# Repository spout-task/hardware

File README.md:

# SPOUT hardware

Hardware for a **SPOUT** rig, part of the [spout-task](https://github.com/spout-task) project.
Every device has its own folder with design files, pictures and a README that explains what it does,
what to buy, how to make it and how to connect it to SPOUT.

A complete rig costs about **1,080 USD** (about 1,440 USD including a computer and screen).
The full bill of materials is in [`SPOUT_BOM.xlsx`](SPOUT_BOM.xlsx) and [`SPOUT_BOM.pdf`](SPOUT_BOM.pdf).

<p align="center"><em>A SPOUT rig seen from above: head restrained setup (left), motorized manipulator with the spouts (center), electronics with the Teensy breakout board (top), water reservoirs (top right) and the stepper motor driver box (right).</em></p>

## Devices

| Group | Device | What it does | How it is made | Folder |
|---|---|---|---|---|
| Electronics | Teensy breakout board | Carries the Teensy 4.1, drives the solenoids and brings out all inputs and outputs | PCB, 3D printed housing | [`teensy_breakout_board`](teensy_breakout_board/) |
| Electronics | Dual lick detector | Detects licks on one or two spouts with sub millisecond precision | PCB, 3D printed housing | [`dual_lick_detector`](dual_lick_detector/) |
| Electronics | Optogenetics power modulator | Turns a Teensy PWM signal into a 0 to 5 V analog command, so light power can be set per trial | Hand built circuit, 3D printed housing | [`optogenetics_power_modulator`](optogenetics_power_modulator/) |
| Head fixation | Head restrained setup | Headplates and holders for behavior and for two photon imaging | Laser cut titanium headplates, machined aluminium holders, ramps and cone | [`head-restrained_setup`](head-restrained_setup/) |
| Head fixation | Breadboards | Rig base plate and round base for the head fixation | Machined aluminium by a machine shop (or bought) | [`breadboards`](breadboards/) |
| Spout positioning | Motorized manipulator | Three axis stepper stage that positions the spouts | Bought stages and drivers, 3D printed adapters, laser cut driver box and drilling templates | [`motorized_manipulator`](motorized_manipulator/) |
| Spout positioning | Spout holder | Holds the stainless steel lick spout(s) and the two solenoid valves | 3D printed spout holders, laser cut solenoid holder | [`spout_holder`](spout_holder/) |
| Miscellaneous | Housings | Boxes for the audio amplifier and for the power distribution breadboard | 3D printed | [`housing_miscellaneous`](housing_miscellaneous/) |

## Build order for one rig

1. **Base.** The 12 x 18 inch breadboard is the base of the rig.
2. **Head fixation.** Build the head restrained setup on the round breadboard: magnetic base, post, clamp, aluminium tube and headplate holders.
3. **Water delivery.** Reservoir syringes, 3 way valves, solenoids in the solenoid holder, Tygon tubing, and the spouts in the spout holder.
4. **Spout positioning.** Stack the three linear stages with the printed adapters, mount the spout holder on a post on the top stage, and put the three drivers in the laser cut box.
5. **Electronics.** Teensy breakout board in its housing, power distribution box, dual lick detector in its housing. Connect the spouts to the lick detector and ground the mouse through the aluminium tube.
6. **Sound.** Audio amplifier in its housing and two speakers on short posts.
7. **Optogenetics (optional).** Optogenetics power modulator between the Teensy and the LED or AOM driver.
8. **Software.** Flash the firmware and open the GUI, see the [software](https://github.com/spout-task/software) repository.

Photos of the build process will be added.

## Conventions

* 3D printed parts: Prusa MK3, PLA, standard settings.
* Screws: 1/4 20 for the breadboards and posts, 4-40 for small parts.
* Units: mm, except the breadboard STEP files (inch). DXF files are in mm.
* Each device folder has a `design` folder with `files` (design files) and `pictures` (renders). Electronics also have a `PCB` or `circuit` folder, and the manipulator a `schematics` folder.
* File types: STL to 3D print, DXF to laser cut, STEP to edit in CAD or to send to a machine shop. Flat parts come as DXF and STL, so you can laser cut or print them.
* Each README lists for every part how we made it and from what material.

## Related repositories
[software](https://github.com/spout-task/software), [analyses](https://github.com/spout-task/analyses), [settings](https://github.com/spout-task/settings), [example_data](https://github.com/spout-task/example_data)

## License
All hardware designs in this repository are released under **CERN-OHL-S-2.0** ([`LICENSE`](LICENSE)).
The dual lick detector and the Teensy breakout board were designed by the
[HMS Research Instrumentation Core](https://github.com/HMS-RIC), whose members are authors of SPOUT,
and are shared here as part of SPOUT. Newer revisions are developed in the HMS RIC repositories for the
[lick detector](https://github.com/HMS-RIC/2-Channel-Lick-Detector) and the
[Teensy breakout board](https://github.com/HMS-RIC/Teensy-Breakout-general-purpose).

## How to cite
See [`CITATION.cff`](CITATION.cff) and the [project overview](https://github.com/spout-task).

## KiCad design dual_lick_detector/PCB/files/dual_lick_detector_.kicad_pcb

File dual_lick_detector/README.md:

# Dual lick detector

Two channel lick detector for head restrained mice. Each lick closes a tiny current path between the
spout and the grounded mouse; the detector turns that into a clean digital pulse for the Teensy, with
sub millisecond precision.

## At a glance

| | |
|---|---|
| Function | Detects licks on one or two spouts |
| Design | HMS Research Instrumentation Core, revision Alpha1e (KiCad 10) |
| Fabrication | PCB with commercial assembly, 3D printed housing |
| Approximate cost | 100 USD for the assembled board |
| Used by | SPOUT1 (one channel) and SPOUT2 (two channels) |

## Key features

* Battery powered, optically isolated front end.
* Adjustable threshold and (optionally) adjustable hysteresis (100 mV default).
* Multi turn potentiometers for fine adjustment; can be fitted with a scale dial.
* Selectable conduction mode or junction potential mode. SPOUT uses conduction mode.
* Power from micro USB or a barrel jack adapter.
* Indicator LEDs for power and lick detection; ESD protected front end.
* Optional input protection diodes to support shock delivery.

## How it works in SPOUT

In conduction mode each spout is pulled up to 9 V (from a 9 V battery) through a 4.7 MOhm resistor.
When the grounded mouse touches the spout, the voltage drops and a comparator switches. The input is
filtered with a 10 us RC filter and the comparator has 100 mV hysteresis. An optically isolated output
stage, powered by a separate 3 V adapter, drives the output through a 50 Ohm source termination, so the
signal can run over BNC cables. In the SPOUT configuration the output is active low.

## Files

| File | What it is |
|---|---|
| [`PCB/files/dual_lick_detector_.kicad_sch`](PCB/files/dual_lick_detector_.kicad_sch) | Schematic (KiCad 10) |
| [`PCB/files/dual_lick_detector_.kicad_pcb`](PCB/files/dual_lick_detector_.kicad_pcb) | Board layout (KiCad 10) |
| [`ComparatorLickDet_BOM.pdf`](ComparatorLickDet_BOM.pdf) | Component list, readable version (made for revision Alpha1d) |
| [`PCB/pictures`](PCB/pictures/) | Photos and board renders, see below |

| Part | Files | What it is | How we made it |
|---|---|---|---|
| Housing | [`.stl`](design/files/box_dual_lick_detector.stl), [`.step`](design/files/box_dual_lick_detector.step) | Housing, 152 x 89 x 20 mm, with mounting ears | 3D printed, PLA |

The SPOUT paper used revision Alpha1d (EAGLE). Alpha1e is the KiCad version of that design.
Newer revisions are developed in the [HMS RIC repository](https://github.com/HMS-RIC/2-Channel-Lick-Detector).

### Pictures

| Picture | What it shows |
|---|---|
| [`dual_lick_detector_1.jpg`](PCB/pictures/dual_lick_detector_1.jpg) | Assembled board with BNC connectors, potentiometers and battery holder |
| [`dual_lick_detector_2.jpg`](PCB/pictures/dual_lick_detector_2.jpg) | Bare board, top |
| [`dual_lick_detector_3.jpg`](PCB/pictures/dual_lick_detector_3.jpg) | Bare board, bottom |
| [`dual_lick_detector_schematic_1.png`](PCB/pictures/dual_lick_detector_schematic_1.png) | Board render from KiCad, bottom |
| [`dual_lick_detector_schematic_2.png`](PCB/pictures/dual_lick_detector_schematic_2.png) | Board render from KiCad, top |

## Bill of materials

| Qty | Part | Supplier | Part number | Price (USD) |
|---|---|---|---|---|
| 1 | Assembled lick detector board | Any PCB assembler (we used PCBWay) | KiCad files | 100 |
| 1 | 3D printed housing | | | |
| 1 | 9 V battery | | | |
| 1 | Power adapter 3 V (output stage) | NC | BY0301&BK | 5.57 |
| 1 | Stainless steel tube for the spouts | McMaster-Carr | 5560K72 | 3.90 |
| 1 | Banana socket and plug (mouse ground) | | | 2.98 |

Full list: [`SPOUT_BOM.xlsx`](../SPOUT_BOM.xlsx).

## Ordering the PCB

The board is designed in KiCad 10. Open the `.kicad_pcb` file in KiCad (free, [kicad.org](https://www.kicad.org)) and export
what your fabricator needs: Gerber and drill files (File, Fabrication Outputs), and for commercial assembly the
component list and the position file from the same menu. Default manufacturing settings are fine.

## Fabrication

1. Order the assembled board as described above. All the fine soldering will be done, you only need to solder big components on the PCB. The SPOUT boards were made and assembled by PCBWay.
2. On both sides of the PCB, solder dual jack BNC connectors in place.
3. On the top side of the PCB, you will have to solder two multi-turn potentiometers in place.
4. On the bottom side of the PCB, a DC barrel jack power connector (3V to send TTL to Teensy) and/or micro USB connector (5V if you want to send a TTL to an Arduino), a two-way toggle switch, and a 9V battery casing should be soldered in place.
5. Print `box_dual_lick_detector.stl` on a Prusa MK3 in PLA with standard settings. Mount the board with 4-40 screws and the housing on the breadboard with 1/4 20 screws.

## Assembly

1. Mount the board in the housing and the housing on the breadboard.
2. Connect the spouts to the inputs, and the outputs to the Teensy breakout board, as listed below.
3. Ground the mouse: connect the detector ground to the aluminium tube of the head restrained setup with the banana plug and socket.
4. Insert the 9 V battery and connect the 3 V adapter.
5. For imaging, split the lick outputs with a BNC T connector to your DAQ as well.

## Connections

Seen from the top, with the potentiometers facing up. Each side has two BNC connectors, one above the other.

| Part | SPOUT2 (two spouts) | SPOUT1 (one spout) |
|---|---|---|
| Left BNC, top | Left lick output, to PIN14_A0 on the Teensy breakout board | Lick output, to PIN14_A0 |
| Left BNC, bottom | Right lick output, to PIN41_A17 | Not used |
| Right BNC, top | Left lick input, from the left spout | Lick input, from the spout |
| Right BNC, bottom | Right lick input, from the right spout | Not used |
| Bottom LED | Left lick detected | Lick detected |
| Top LED | Right lick detected | Not used |
| Left potentiometer | Left lick threshold | Lick threshold |
| Right potentiometer | Right lick threshold | Not used |

## Testing and calibration

1. Touch a spout with one hand while touching the ground (aluminium tube) with the other: the lick LED lights up and the GUI shows the lick.
2. Set the threshold with the multi turn potentiometer (left for the left spout, right for the right spout) so a touch is detected reliably while the idle spout stays silent. Set it per rig, because cable length and grounding differ.

## License and attribution
Designed and developed by the [HMS Research Instrumentation Core](https://github.com/HMS-RIC), whose
members are authors of SPOUT, and shared here as part of SPOUT under **CERN-OHL-S-2.0**
([`LICENSE`](../LICENSE)). Newer revisions are developed in the
[HMS RIC repository](https://github.com/HMS-RIC/2-Channel-Lick-Detector).

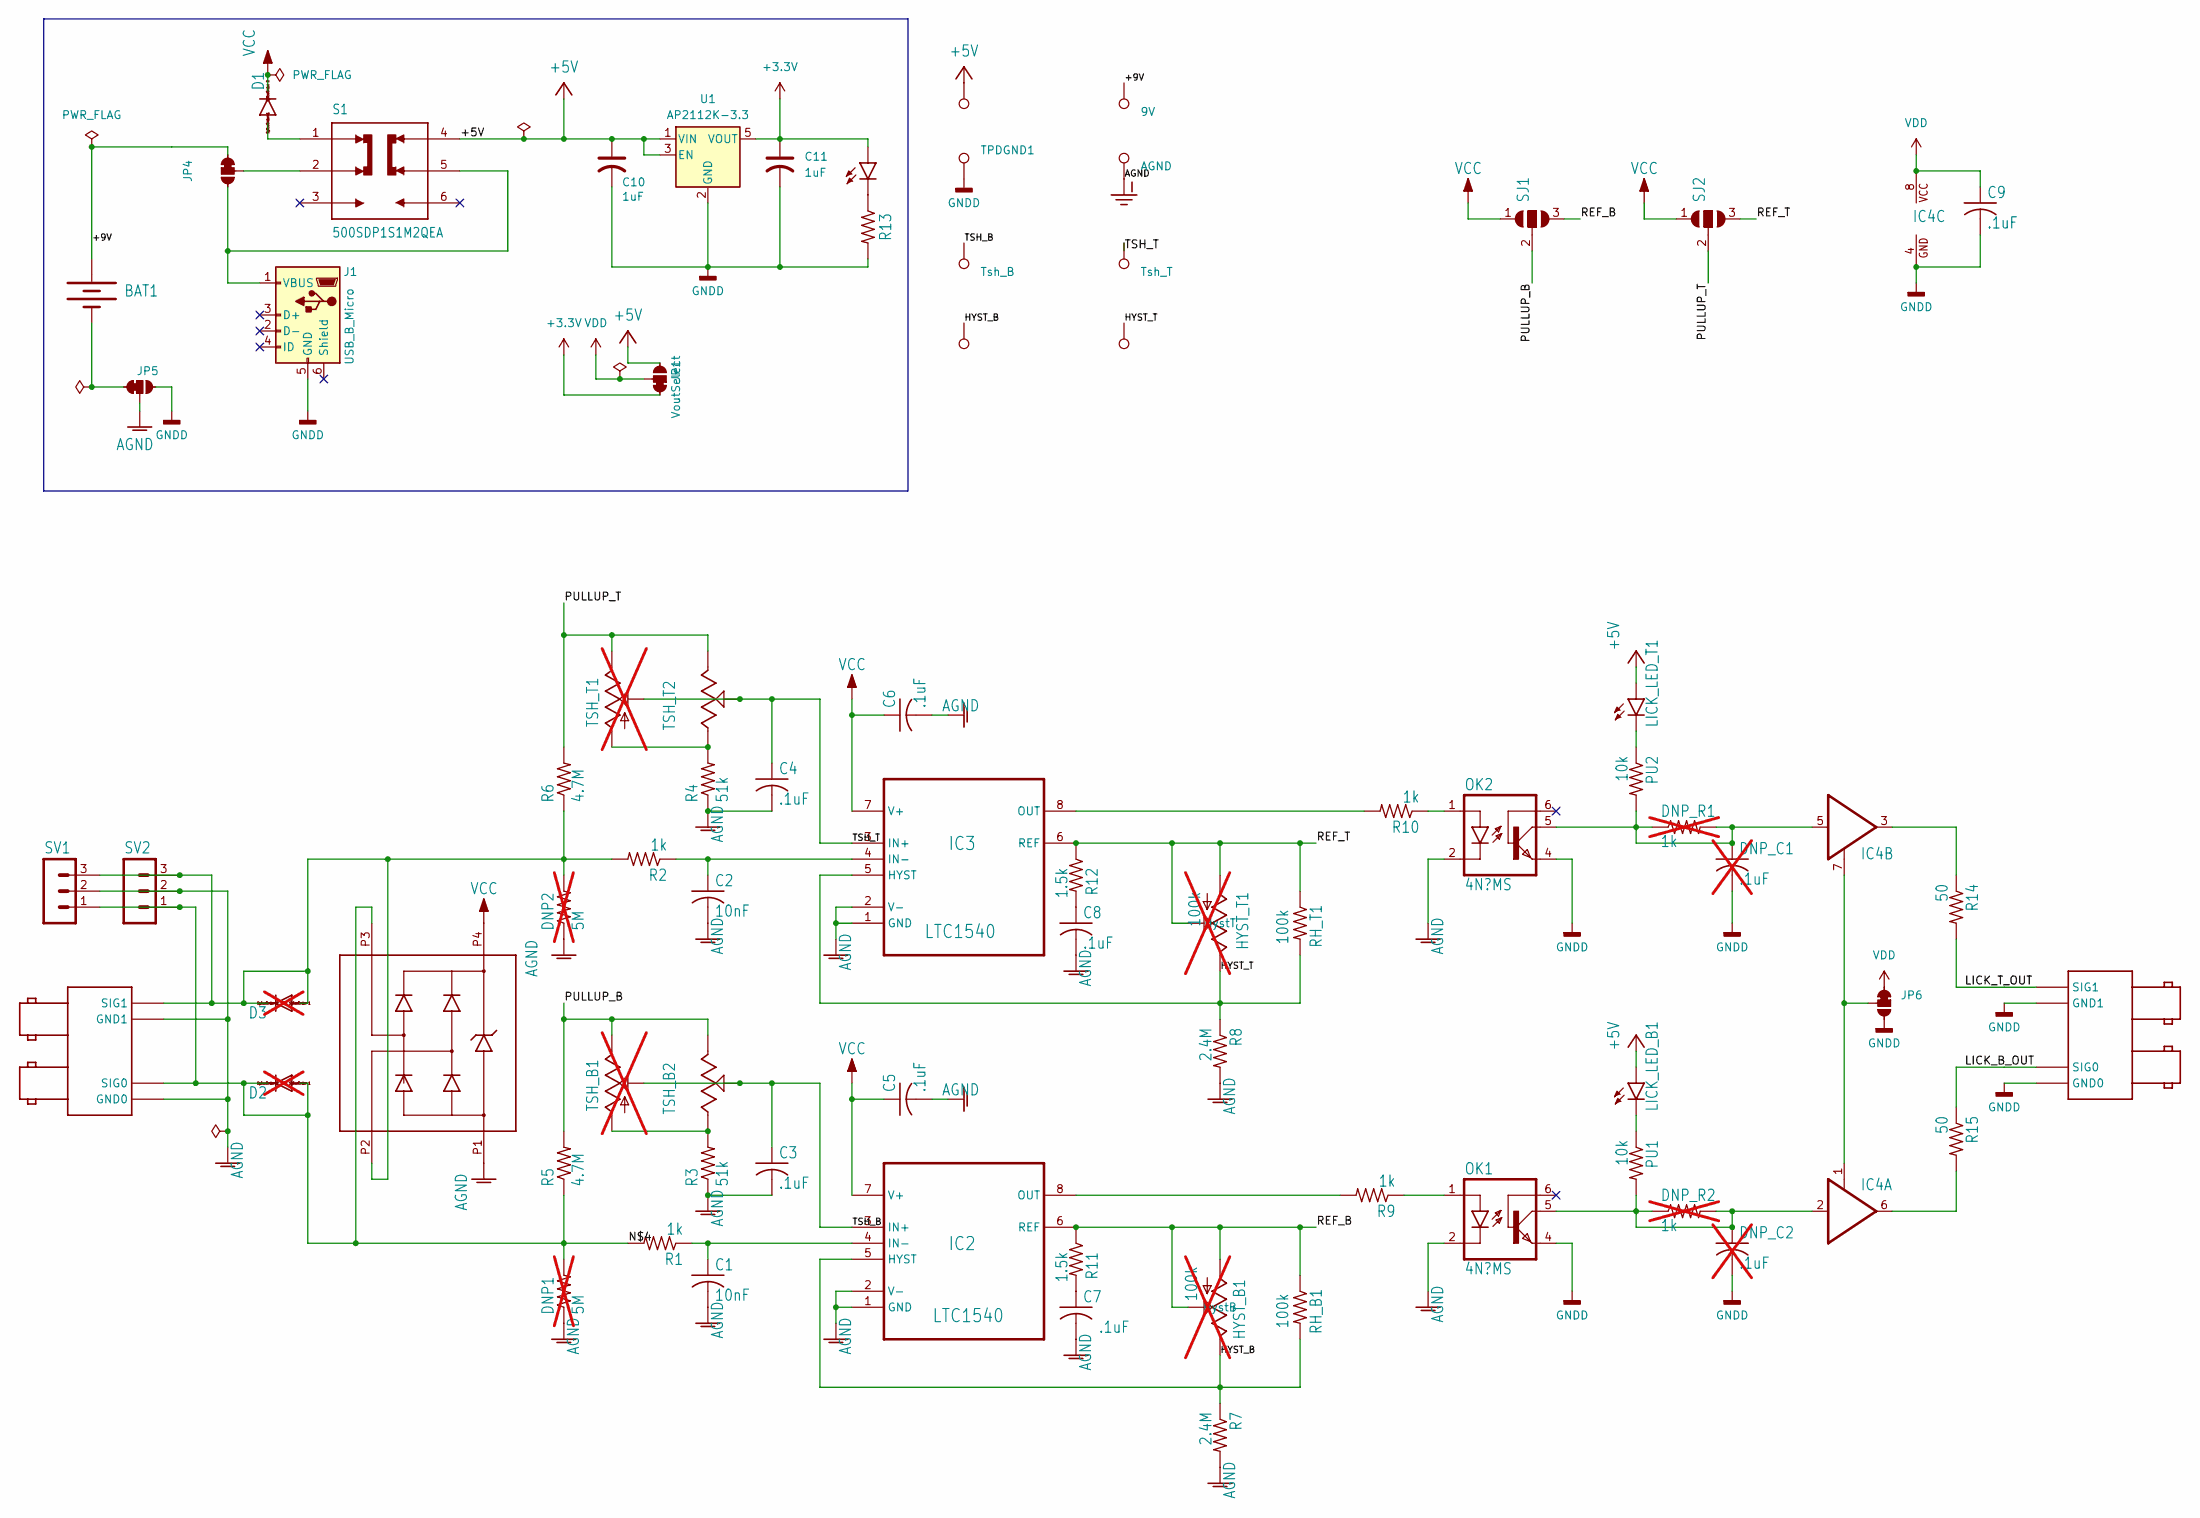
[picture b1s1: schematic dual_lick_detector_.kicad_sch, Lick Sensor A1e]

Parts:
BAT1: BATTERY9V; BATTCON_9V
C1, C2: 10nF; C0805
C3, C4, C5, C6, C7, C8, C9: .1uF; C0805
C10, C11: 1uF; C0805
D1: DIODE-DO-214AC; DO-214AC
D2, D3: DIODE-D-2.5; D-2.5; not fitted
DNP1, DNP2: 5M; M0805; not fitted
DNP_C1, DNP_C2: .1uF; C0805; not fitted
DNP_R1, DNP_R2: 1k; M0805; not fitted
HYST_B1: 100k; B25P; not fitted
HYST_T1: 100k; B25P; not fitted
IC1: CD143A-12_TVS; SOT-143
IC2, IC3: LTC1540; SOIC127P600X175-8N
IC4: SN74LVC2G126DCT; DCT_R-PDSO-G8
J1: USB_B_Micro; USB_Micro-B_Amphenol_10103594-0001LF_Horizontal
JP1: VoutSelect; Jumper_3_NC-1_Trace_NoSilk
JP4, JP5, JP6: Jumper_3_NC-1_Trace_NoSilk
LICKS_IN1: Licks_In; BNC_RIGHT_ANGLE_DOUBLE
LICKS_OUT1: Licks_Out; BNC_RIGHT_ANGLE_DOUBLE
LICK_LED_B1: BLick_LED; CHIPLED_0805
LICK_LED_T1: TLick_LED; CHIPLED_0805
OK1, OK2: 4N?MS; DIL6-SMD
PU1, PU2: 10k; M0805
PWR_LED1: PWR; CHIP-LED0805
R1, R2, R9, R10, R13: 1k; M0805
R3, R4: 51k; M0805
R5, R6: 4.7M; M0805
R7, R8: 2.4M; M0805
R11, R12: 1.5k; M0805
R14, R15: 50; M0805
RH_B1: 100k; M0805
RH_T1: 100k; M0805
S1: 500SDP1S1M2QEA; SW_500SDP1S1M2QEA
SJ1, SJ2: SJ2W; SJ_2
SV1, SV2: MA03-1
TP5V1: 5V; TestPoint_THTPad_2.0x2.0mm_Drill1.0mm
TP9V1: 9V; TestPoint_THTPad_2.0x2.0mm_Drill1.0mm
TPAGND1: AGND; TestPoint_THTPad_2.0x2.0mm_Drill1.0mm
TPDGND1: DGND; TestPoint_THTPad_2.0x2.0mm_Drill1.0mm
TP_Hyst_B1: Hyst_B; TestPoint_THTPad_D2.0mm_Drill1.0mm
TP_Hyst_T1: Hyst_T; TestPoint_THTPad_D2.0mm_Drill1.0mm
TP_TSH_B1: Tsh_B; TestPoint_THTPad_D2.0mm_Drill1.0mm
TP_TSH_T1: Tsh_T; TestPoint_THTPad_D2.0mm_Drill1.0mm
TSH_B1: 100k; B25P; not fitted
TSH_B2: 3590S-2-103L; TRIM_3590S-2-103L
TSH_T1: 100k; B25P; not fitted
TSH_T2: 3590S-2-103L; TRIM_3590S-2-103L
U1: AP2112K-3.3; SOT-23-5

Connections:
+3.3V: C11.1, JP1.1 (A), PWR_LED1.A, U1.5 (VOUT)
+5V: C10.1, JP1.3 (C), LICK_LED_B1.A, LICK_LED_T1.A, S1.4, TP5V1.1, U1.1 (VIN), U1.3 (EN)
/+9V: BAT1.+, JP4.1 (A), TP9V1.1
/HYST_B: HYST_B1.E, IC2.5 (HYST), R7.1, RH_B1.2, TP_Hyst_B1.1
/HYST_T: HYST_T1.E, IC3.5 (HYST), R8.1, RH_T1.2, TP_Hyst_T1.1
/LICK_B_OUT: LICKS_OUT1.P$SIG0 (SIG0), R15.1
/LICK_T_OUT: LICKS_OUT1.P$SIG1 (SIG1), R14.2
/N$4: D2.A, D2.C, DNP1.2, IC1.P3, LICKS_IN1.P$SIG0 (SIG0), R1.2, R5.1, SV1.1, SV2.1
/PULLUP_B: R5.2, SJ1.2, TSH_B1.E, TSH_B2.3 (CW)
/PULLUP_T: R6.2, SJ2.2, TSH_T1.E, TSH_T2.3 (CW)
/REF_B: HYST_B1.A, HYST_B1.S, IC2.6 (REF), R11.1, RH_B1.1, SJ1.3
/REF_T: HYST_T1.A, HYST_T1.S, IC3.6 (REF), R12.1, RH_T1.1, SJ2.3
/TSH_B: C3.1, IC2.3 (IN+), TP_TSH_B1.1, TSH_B1.S, TSH_B2.2 (WIPER)
/TSH_T: C4.1, IC3.3 (IN+), TP_TSH_T1.1, TSH_T1.S, TSH_T2.2 (WIPER)
AGND: C1.2, C2.2, C3.2, C4.2, C5.2, C6.2, C7.2, C8.2, DNP1.1, DNP2.1, IC1.P1, IC2.1 (GND), IC2.2 (V-), IC3.1 (GND), IC3.2 (V-), JP5.2 (B), LICKS_IN1.P$GND0 (GND0), LICKS_IN1.P$GND1 (GND1), OK1.2 (C), OK2.2 (C), R3.1, R4.1, R7.2, R8.2, SV1.2, SV2.2, TPAGND1.1
GNDD: C9.2, C10.2, C11.2, DNP_C1.2, DNP_C2.2, IC4.4 (GND), J1.5 (GND), JP5.3 (C), JP6.3 (C), LICKS_OUT1.P$GND0 (GND0), LICKS_OUT1.P$GND1 (GND1), OK1.4 (EMI), OK2.4 (EMI), R13.2, TPDGND1.1, U1.2 (GND); also elsewhere on the board
unnamed: C7.1, R11.2
unnamed: C8.1, R12.2
unnamed: D1.A, S1.1
unnamed: D3.A, D3.C, DNP2.2, IC1.P2, LICKS_IN1.P$SIG1 (SIG1), R2.2, R6.1, SV1.3, SV2.3
unnamed: C1.1, IC2.4 (IN-), R1.1
unnamed: IC2.8 (OUT), R9.2
unnamed: C2.1, IC3.4 (IN-), R2.1
unnamed: IC3.8 (OUT), R10.2
unnamed: DNP_C2.1, DNP_R2.1, DNP_R2.2, IC4.2 (I), OK1.5 (COL), PU1.2
unnamed: IC4.6 (O), R15.2
unnamed: IC4.1 (OE), IC4.7 (OE), JP6.2 (B)
unnamed: DNP_C1.1, DNP_R1.1, DNP_R1.2, IC4.5 (I), OK2.5 (COL), PU2.2
unnamed: IC4.3 (O), R14.1
unnamed 29: J1.1 (VBUS), JP4.3 (C), S1.5; also elsewhere on the board
unnamed: JP4.2 (B), S1.2
unnamed: BAT1.-, JP5.1 (A)
unnamed: LICK_LED_B1.C, PU1.1
unnamed: LICK_LED_T1.C, PU2.1
unnamed: OK1.1 (A), R9.1
unnamed: OK2.1 (A), R10.1
unnamed: PWR_LED1.C, R13.1
unnamed: R3.2, TSH_B1.A, TSH_B2.1 (CCW)
unnamed: R4.2, TSH_T1.A, TSH_T2.1 (CCW)
VCC: C5.1, C6.1, D1.C, IC1.P4, IC2.7 (V+), IC3.7 (V+), SJ1.1, SJ2.1
VDD: C9.1, IC4.8 (VCC), JP1.2 (B), JP6.1 (A)

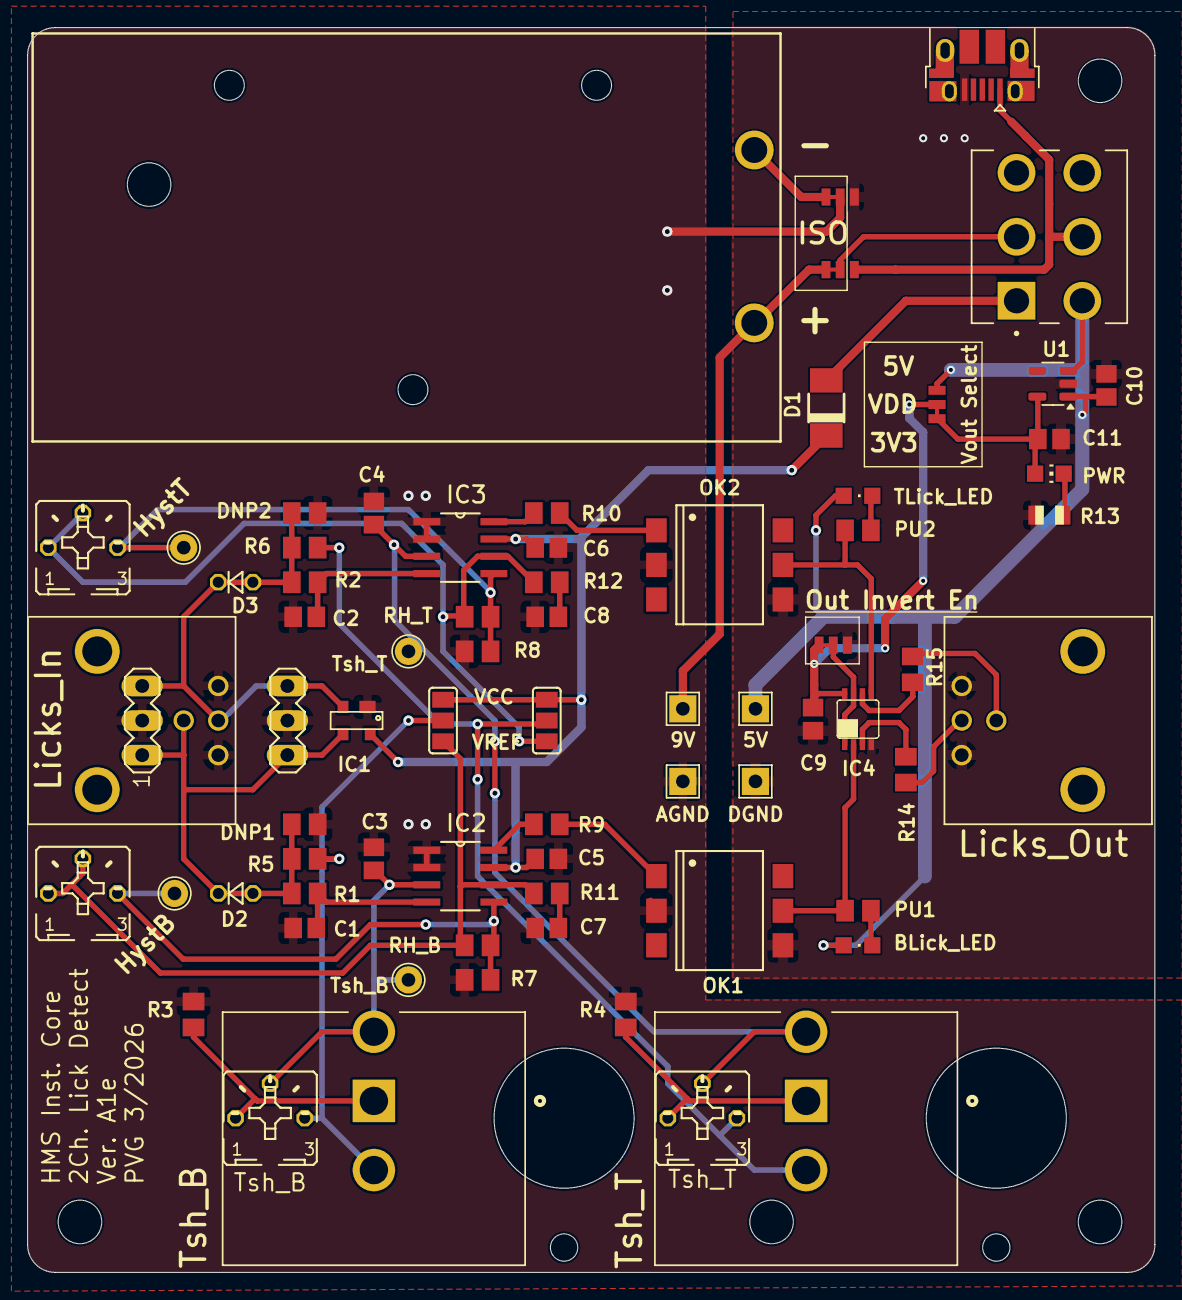
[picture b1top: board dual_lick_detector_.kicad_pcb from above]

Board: 2 copper layers, 82.8 x 91.4 mm, 82 parts (1 on the bottom side), 41 nets.

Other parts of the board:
@HOLE0, @HOLE1, @HOLE2, @HOLE3, @HOLE4, @HOLE5, @HOLE6, @HOLE7, @HOLE8: (no value)
J2: USB_B_Micro; USB_Micro-B_Amphenol_10103594-0001LF_Horizontal
U$7: RIC_LOGO_BIG

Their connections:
GNDD: J2.5 (GND); also elsewhere on the board
unnamed 29: J2.1 (VBUS); also elsewhere on the board

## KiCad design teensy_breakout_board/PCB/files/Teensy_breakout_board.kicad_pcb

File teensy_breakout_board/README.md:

# Teensy breakout board

This general breadkout board carries the Teensy 4.1 that runs the SPOUT state machine,
drives the water solenoids, and brings every input and output to a BNC connector or a header.

## At a glance

| | |
|---|---|
| Function | Teensy 4.1 carrier with solenoid drivers and BNC inputs and outputs |
| Design | HMS Research Instrumentation Core, revision Alpha1b (KiCad 10) |
| Fabrication | PCB, Teensy in a socket, 3D printed housing |
| Approximate cost | 100 USD for the assembled board |
| Used by | SPOUT1 and SPOUT2 |

## Files

| File | What it is |
|---|---|
| [`PCB/files/Teensy_breakout_board.kicad_sch`](PCB/files/Teensy_breakout_board.kicad_sch) | Schematic (KiCad 10) |
| [`PCB/files/Teensy_breakout_board.kicad_pcb`](PCB/files/Teensy_breakout_board.kicad_pcb) | Board layout (KiCad 10) |
| [`PCB/pictures`](PCB/pictures/) | Photos and board renders, see below |

| Part | Files | What it is | How we made it |
|---|---|---|---|
| Housing | [`.stl`](design/files/box_teensy_breakoutboard.stl), [`.step`](design/files/box_teensy_breakoutboard.step) | Housing, 152 x 106 x 20 mm | 3D printed, PLA |

The SPOUT paper used revision Alpha1b (KiCad 10), the version in this folder.
Newer revisions are developed in the [HMS RIC repository](https://github.com/HMS-RIC/Teensy-Breakout-general-purpose).

### Pictures

| Picture | What it shows |
|---|---|
| [`Teensy_breakout_board_1.jpg`](PCB/pictures/Teensy_breakout_board_1.jpg) | Assembled board with the Teensy 4.1 and eight BNC connectors |
| [`Teensy_breakout_board_2.jpg`](PCB/pictures/Teensy_breakout_board_2.jpg) | Bare board, top |
| [`Teensy_breakout_board_3.jpg`](PCB/pictures/Teensy_breakout_board_3.jpg) | Bare board, bottom |
| [`Teensy_breakout_board_schematic_1.png`](PCB/pictures/Teensy_breakout_board_schematic_1.png) | Board render from KiCad, top |
| [`Teensy_breakout_board_schematic_2.png`](PCB/pictures/Teensy_breakout_board_schematic_2.png) | Board render from KiCad, bottom |

## Bill of materials

| Qty | Part | Supplier | Part number | Price (USD) |
|---|---|---|---|---|
| 1 | Assembled breakout board including Teensy 4.1 | | | 100 |
| 1 | 3D printed housing | | | |
| 1 | Power adapter 5 V for the solenoids | MTYTOT | ALT-0503 | 6.99 |
| 2 | Solenoid valve, 5 V | The Lee Company | LHQA0531220H | 65.60 each |
| 5 | BNC cable, 50 Ohm, 3 feet | | | 5.63 each |

Full list: [`SPOUT_BOM.xlsx`](../SPOUT_BOM.xlsx).

## Ordering the PCB

The board is designed in KiCad 10. Open the `.kicad_pcb` file in KiCad (free, [kicad.org](https://www.kicad.org)) and export
what your fabricator needs: Gerber and drill files (File, Fabrication Outputs), and for commercial assembly the
component list and the position file from the same menu. Default manufacturing settings are fine.

## Fabrication

1. Order the board as described above. No components will be soldered on. The SPOUT boards were made by PCBWay.
2. Solder female headers (24) left and right on the board. If the Teensy came without headers, solder male headers (24 left and right) on the Teensy 4.1, so the Teensy can be swapped.
3. Solder four BNC connector plugs on the left and right side of the board.
4. Solder two 361 resistors (360 ohms) on R6 and R7 (for left and right solenoids).
5. Solder two 114 resistors (110 kOhm) on R9 nad R10 (for left and right solenoids).
6. Solder two Onsemi mosfets (NCV8406ASTT1G) on T1 and T2 (for left and right solenoids).
7. Solder two male 2-pin PCB connectors to SLN1 and SLN2 (for left and right solenoids).
8. Optional: solder female headers to the left (12), right (12), and far right (4) of the Teensy. Use these if you need more Teensy pin access than the 8 BNC connectors.
9. Print `box_teensy_breakoutboard.stl` on a Prusa MK3 in PLA with standard settings. Mount the board with 4-40 screws and the housing on the breadboard with 1/4 20 screws.
10. For additional purposes (buttons, extra solenoid, servo, etc), see "Expansion options" below.

## Assembly

1. Insert the Teensy 4.1 in its socket.
2. Connect the 5 V adapter to the solenoid supply input. The Teensy itself is powered over USB from the computer, so the solenoid supply and the Teensy supply stay separate.
3. Make the connections listed below for SPOUT1 or SPOUT2.
4. Connect the remaining TTL outputs you need (see the pin map) from the headers to your acquisition system.
5. Connect the Teensy to the computer by USB and flash the firmware (see [software](https://github.com/spout-task/software)).

## Connections

The BNC connectors are labelled on the board with the Teensy pin and their function.

**SPOUT1**

| Board connector | Connect to |
|---|---|
| PIN2_S2 | Tone (amplifier input) |
| PIN3_S1 | Sync pulse (to your acquisition system) |
| PIN5_SLN1 | TTL of the solenoid command |
| PIN14_A0 | Lick (from the lick detector output) |
| PIN40_A16 | Optogenetics driver |
| SLN1 | Solenoid |

**SPOUT2**

| Board connector | Connect to |
|---|---|
| PIN2_S2 | Left tone (amplifier input) |
| PIN15_A1 | Right tone (amplifier input) |
| PIN3_S1 | Sync pulse (to your acquisition system) |
| PIN5_SLN1 | TTL of the left solenoid command |
| PIN4_SLN2 | TTL of the right solenoid command |
| PIN14_A0 | Left lick (from the lick detector) |
| PIN41_A17 | Right lick (from the lick detector) |
| PIN40_A16 | Optogenetics driver |
| SLN1 | Left solenoid |
| SLN2 | Right solenoid |

Photos of the build process will be added.

## Pin map

Which Teensy pin is on which connector of the board (revision Alpha1b), and what SPOUT uses it for.
The firmware options for every pin are explained in the software READMEs for
[SPOUT1](https://github.com/spout-task/software/tree/main/SPOUT1) and
[SPOUT2](https://github.com/spout-task/software/tree/main/SPOUT2).

| Teensy pin | Board connector | SPOUT2 (two spouts) | SPOUT1 (one spout) |
|---|---|---|---|
| 2 | BNC PIN2_S2, header SV1 | Left speaker | Speaker A |
| 3 | BNC PIN3_S1, header SV1 | Sync pulse output (pseudo random) | Sync pulse output |
| 4 | BNC PIN4_SLN2, solenoid driver SLN2, header SV1 | Right solenoid | Not used |
| 5 | BNC PIN5_SLN1, solenoid driver SLN1, header SV1 | Left solenoid | Solenoid |
| 14 (A0) | BNC PIN14_A0, header SV2 | Left lick input | Lick input |
| 15 (A1) | BNC PIN15_A1, header SV2 | Right speaker | Speaker B (optional) |
| 40 (A16) | BNC PIN40_A16 | Optogenetics TTL | Optogenetics TTL |
| 41 (A17) | BNC PIN41_A17 | Right lick input | Not used |
| 1 | Header SV1 | Optogenetics copy (reporter LED) | Optogenetics copy |
| 6 | Header SV1, SERVO1 | Speaker TTL | Speaker TTL |
| 7 | Header SV1, SERVO2 | Trial start TTL | Trial start TTL |
| 8 | Header SV1 | ITI TTL | ITI TTL |
| 9 | Header SV1 | Optogenetics power modulation (PWM) | Optogenetics power modulation (PWM) |
| 10 | Board LED10 | Session start and stop pulse | Session start and stop pulse |
| 11 | Board LED11 | Camera trigger (2 ms pulses at 50 Hz) | Off |
| 12 | Board LED12 | External sync report | External sync report |
| 13 | SLN3 position (driver not fitted) | Error light | Off |
| 16 (A2) | Header SV2, potentiometer | Start cue TTL | Not used |
| 17 (A3) | Header SV2 | Left cue TTL | Cue A TTL |
| 18 (A4) | Header SV2, Qwiic SDA | Right cue TTL | Cue B TTL |
| 19 (A5) | Header SV2, Qwiic SCL | Left reward TTL | Reward TTL |
| 20 (A6) | Header SV2 | Right reward TTL | Not used |
| 21 (A7) | Header SV2 | Random background light | Random background light |
| 22 (A8) | Header SV2 | External sync input (3.3 V maximum) | External sync input (3.3 V maximum) |
| 23 (A9) | Header SV2 | Start cue speaker | Not used |
| 24 | Teensy pin only | Delay TTL (delayed response task) | Not used |
| 37, 38, 39 | Teensy pins only | Optional hardware buttons | Off |

Header SV1 carries pins 0 to 9, header SV2 carries pins 14 to 23, and header SV4 carries 3.3 V,
VCC and ground. Pins marked "Teensy pin only" are not on a header of this revision; solder a wire to
the Teensy if you need them. All signals are 3.3 V logic. The Teensy 4.1 is not 5 V tolerant, so never
connect a 5 V signal to an input.

## Expansion options

The board has more on it than SPOUT uses. These parts are free for your own extensions:

* **Third solenoid driver (SLN3).** Pin 13 has a place for a third driver, not fitted on the SPOUT boards. Fit the MOSFET (T3), the flyback diode (D3) and the two resistors (R8, R11) with the same parts as SLN1 and SLN2 to switch a third valve, or a 5 V light such as the SPOUT2 error light.
* **Manual flush.** Headers FLUSH1 and FLUSH2 sit across the SLN1 and SLN2 drivers. A push button on a FLUSH header is meant to open that valve without the Teensy, for example to fill or rinse the lines.
* **Push buttons S1 and S2.** On pins 3 and 2, with pull up resistors. SPOUT uses these pins as sync and speaker outputs, but pin map can be changed.
* **Servo headers SERVO1 and SERVO2.** Signal on pins 6 and 7, powered from VCC. SPOUT uses pins 6 and 7 as TTL outputs.
* **Potentiometer.** On pin 16 (A2), between 3.3 V and ground, for example to set a parameter by hand.
* **Qwiic connectors J1 and J6.** I2C on pins 18 (SDA) and 19 (SCL) for Qwiic sensors. SPOUT uses these pins as TTL outputs, and you should check the connector pinout against the schematic before plugging in a Qwiic device.
* **Indicator LEDs.** LED10, LED11 and LED12 light up with pins 10, 11 and 12.
* **Free pins.** Pin 0 (header SV1) is free in both firmwares; SPOUT1 also leaves pins 11, 13, 16, 23 and 24 free.

SPOUT does not use the Qwiic, servo, potentiometer, push button or FLUSH connectors.

## Testing

1. Open the GUI and give a manual reward: the solenoid clicks and the reward TTL goes high.
2. Touch a spout while the mouse ground is connected: the lick appears in the GUI.
3. Start a session and check the sync pulses on pin 3 with your acquisition system.

## License and attribution
Designed and developed by the [HMS Research Instrumentation Core](https://github.com/HMS-RIC), whose
members are authors of SPOUT, and shared here as part of SPOUT under **CERN-OHL-S-2.0**
([`LICENSE`](../LICENSE)). Newer revisions are developed in the
[HMS RIC repository](https://github.com/HMS-RIC/Teensy-Breakout-general-purpose).

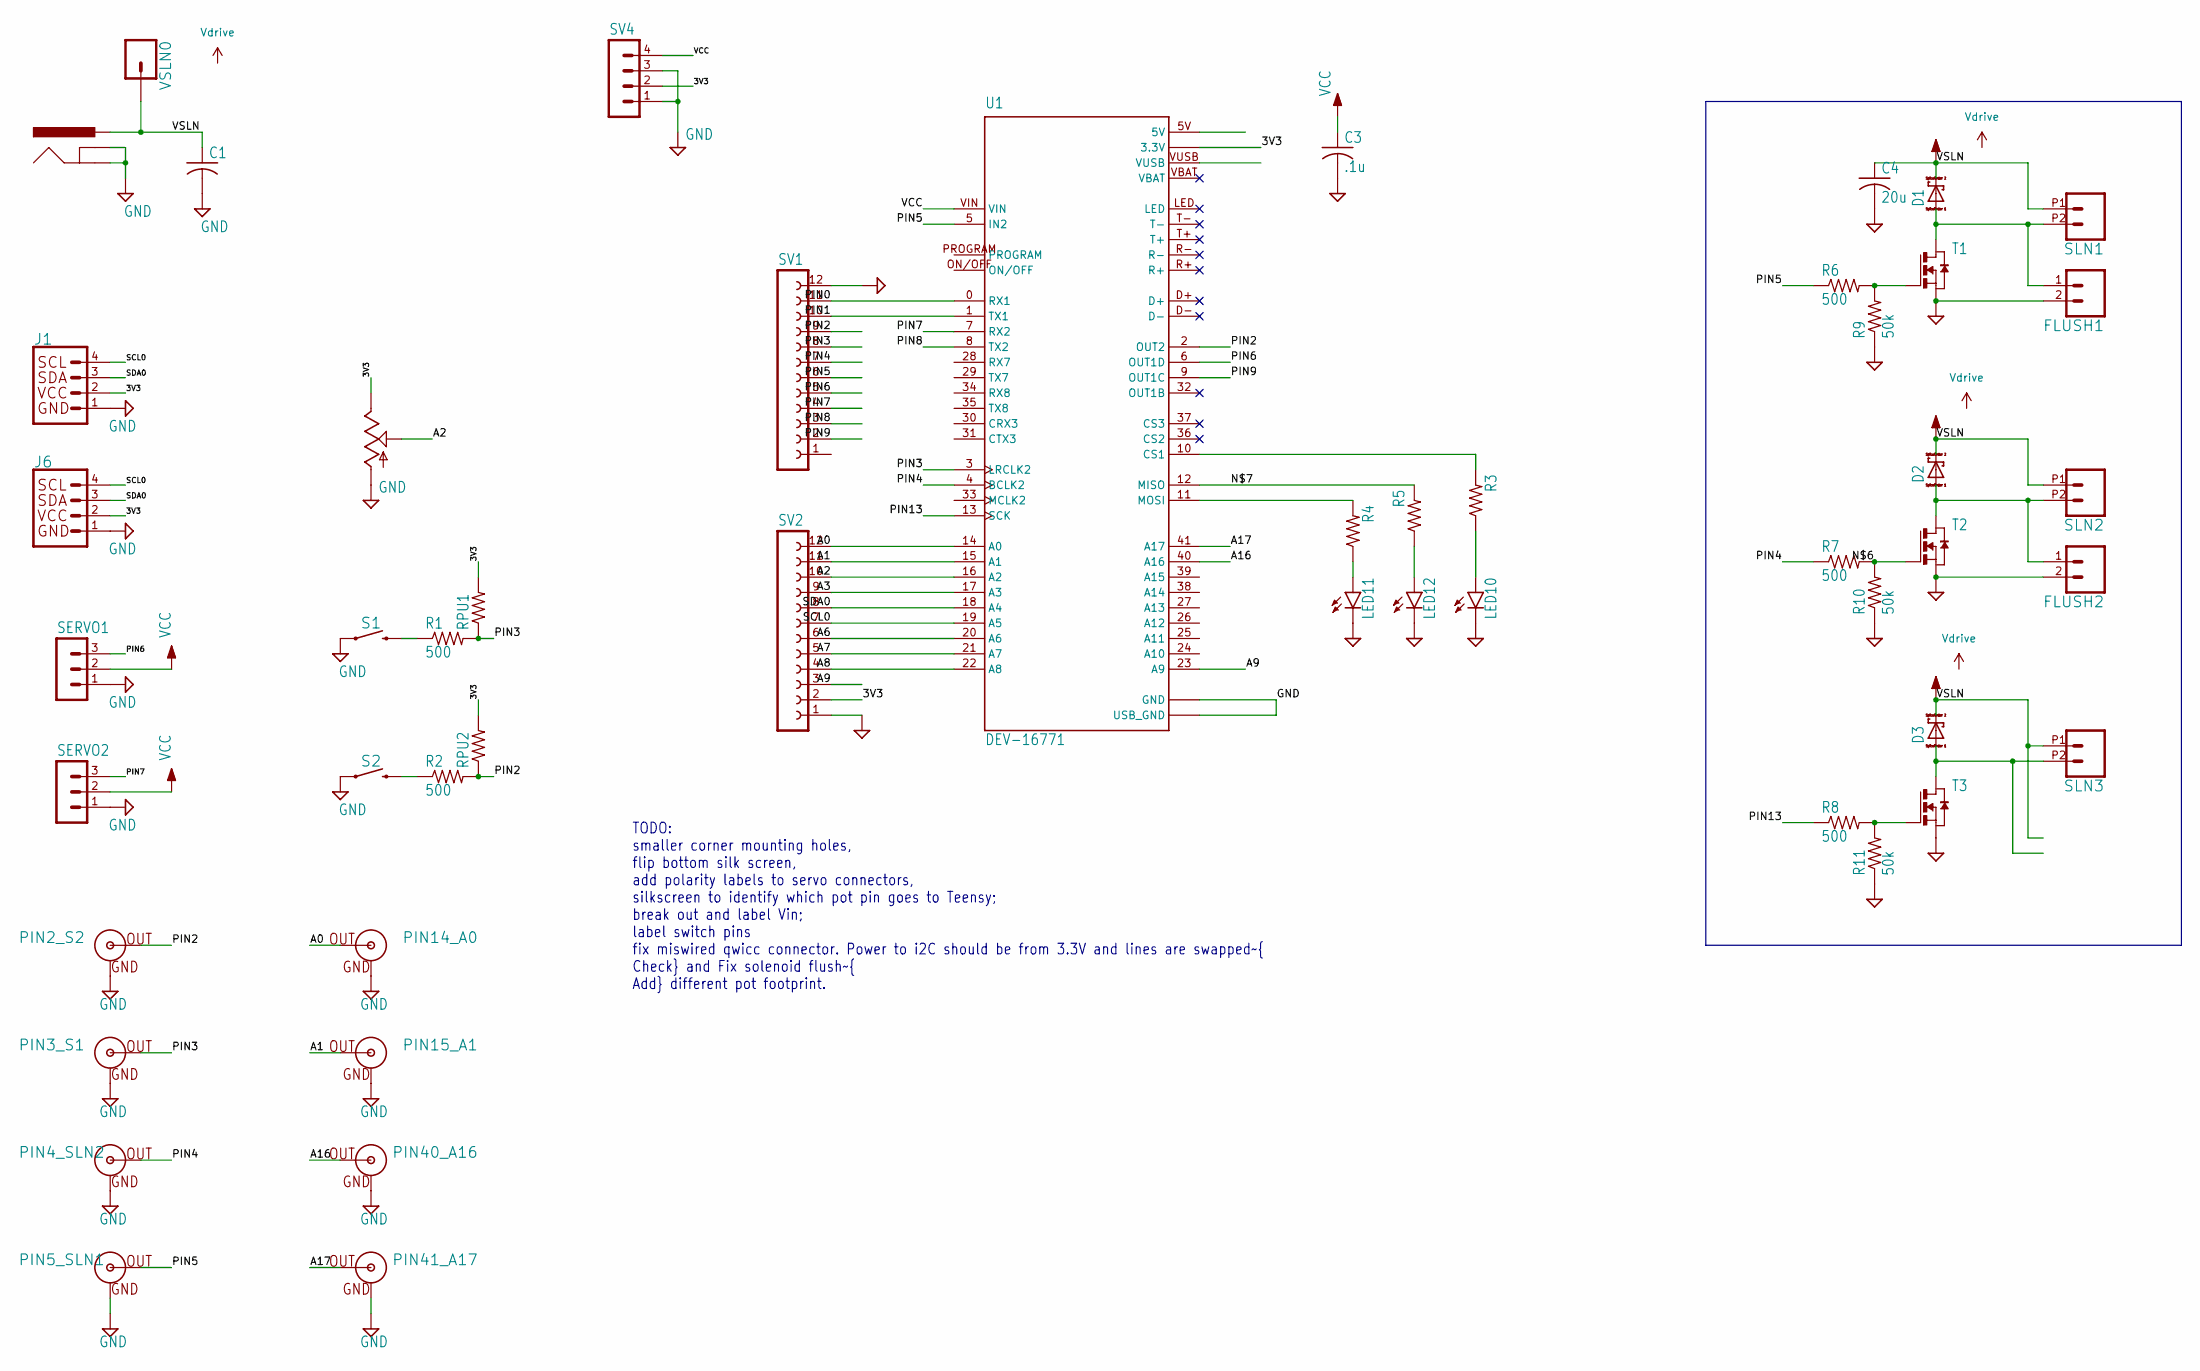
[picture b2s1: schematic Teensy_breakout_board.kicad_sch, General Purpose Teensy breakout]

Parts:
C1: C-US025-024X044; C025-024X044
C3: .1u; C0805K
C4: 20u; C025-040X050
D1, D2, D3: SCHOTTKY-DIODE; DIODE_SMB
FLUSH1, FLUSH2: CONN_02PTH4; 1X02_XTRA_BIG
J1, J6: QWIIC_CONNECTORJS-1MM; 1X04_1MM_RA
J2: POWER_JACK; POWER_JACK_PTH
LED10, LED11, LED12: LEDSFH482; SFH482
PIN2_S2, PIN3_S1, PIN4_SLN2, PIN5_SLN1, PIN14_A0, PIN15_A1, PIN40_A16, PIN41_A17: BNCPTH; BNC
R1, R2: 500; 0207_2V
R3, R4, R5: R-US_0207/2V; 0207_2V
R6, R7, R8: 500; M1206
R9, R10, R11: 50k; M1206
RPU1, RPU2: R-US_0207/2V; 0207_2V
S1, S2: MOMENTARY-SWITCH-SPST-PTH-12MM; TACTILE_SWITCH_PTH_12MM
SERVO1, SERVO2: MA03-1
SLN1, SLN2, SLN3: CONN_022.54MM_SCREWTERM; 1X02_2.54_SCREWTERM
SV1, SV2: FE12-1; FE12
SV4: MA04-1
T1, T2, T3: NMOSSOT223; SOT223
U1: DEV-16771; MODULE_DEV-16771
U$2: POTENTIOMETER; BOURNS_12MM_POTENTIOMETER_VERT
VSLN0: CONN_01; 1X01

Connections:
3V3: J1.2 (VCC), J6.2 (VCC), RPU1.2, RPU2.2, SV2.2, SV4.2, U1.3.3V_1 (3.3V), U1.3.3V_2 (3.3V), U1.3.3V_3 (3.3V), U$2.P$3 (E)
A0: PIN14_A0.S (OUT), SV2.12, U1.14 (A0)
A1: PIN15_A1.S (OUT), SV2.11, U1.15 (A1)
A2: SV2.10, U1.16 (A2), U$2.P$2 (S)
A3: SV2.9, U1.17 (A3)
A6: SV2.6, U1.20 (A6)
A7: SV2.5, U1.21 (A7)
A8: SV2.4, U1.22 (A8)
A9: SV2.3, U1.23 (A9)
A16: PIN40_A16.S (OUT), U1.40 (A16)
A17: PIN41_A17.S (OUT), U1.41 (A17)
GND: C1.2, C3.2, C4.2, FLUSH1.2, FLUSH2.2, J1.1 (GND), J2.GND, J2.GNDBREAK, J6.1 (GND), LED10.K (C), LED11.K (C), LED12.K (C), PIN2_S2.GND, PIN3_S1.GND, PIN4_SLN2.GND, PIN5_SLN1.GND, PIN14_A0.GND, PIN15_A1.GND, PIN40_A16.GND, PIN41_A17.GND, R9.1, R10.1, R11.1, S1.1, S2.1, SERVO1.1, SERVO2.1, SV1.12, SV2.1, SV4.1, SV4.3, T1.3 (S), T2.3 (S), T3.3 (S), U1.GND1 (GND), U1.GND2 (GND), U1.GND3 (GND), U1.GND4 (GND), U1.GND5 (GND), U1.USB_GND1 (USB_GND), U1.USB_GND2 (USB_GND), U$2.P$1 (A)
unnamed: R1.1, S1.3 (2)
unnamed: R2.1, S2.3 (2)
unnamed: R4.2, U1.11 (MOSI)
unnamed: R3.2, U1.10 (CS1)
unnamed: LED10.A, R3.1
unnamed: R7.2, R10.2, T2.1 (G)
unnamed: R5.2, U1.12 (MISO)
unnamed: LED11.A, R4.1
unnamed: LED12.A, R5.1
unnamed: R6.2, R9.2, T1.1 (G)
unnamed: R8.2, R11.2, T3.1 (G)
PIN0: SV1.11, U1.0 (RX1)
PIN1: SV1.10, U1.1 (TX1)
PIN2: PIN2_S2.S (OUT), R2.2, RPU2.1, SV1.9, U1.2 (OUT2)
PIN3: PIN3_S1.S (OUT), R1.2, RPU1.1, SV1.8, U1.3 (LRCLK2)
PIN4: PIN4_SLN2.S (OUT), R7.1, SV1.7, U1.4 (BCLK2)
PIN5: PIN5_SLN1.S (OUT), R6.1, SV1.6, U1.5 (IN2)
PIN6: SERVO1.3, SV1.5, U1.6 (OUT1D)
PIN7: SERVO2.3, SV1.4, U1.7 (RX2)
PIN8: SV1.3, U1.8 (TX2)
PIN9: SV1.2, U1.9 (OUT1C)
PIN13: R8.1, U1.13 (SCK)
SCL0: J1.4 (SCL), J6.4 (SCL), SV2.7, U1.19 (A5)
SDA0: J1.3 (SDA), J6.3 (SDA), SV2.8, U1.18 (A4)
VOUT-1: D2.A (C), FLUSH2.1, SLN2.P2 (2), T2.2 (D), T2.4 (D)
VOUT-2: D1.A (C), FLUSH1.1, SLN1.P2 (2), T1.2 (D), T1.4 (D)
VOUT-3: D3.A (C), SLN3.P2 (2), T3.2 (D), T3.4 (D)

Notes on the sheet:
TODO: smaller corner mounting holes, flip bottom silk screen, add polarity labels to servo connectors, silkscreen to identify which pot pin goes to Teensy; break out and label Vin; label switch pins fix miswired qwicc connector. Power to i2C should be from 3.3V~{} and lines are swapped~{ Check} and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

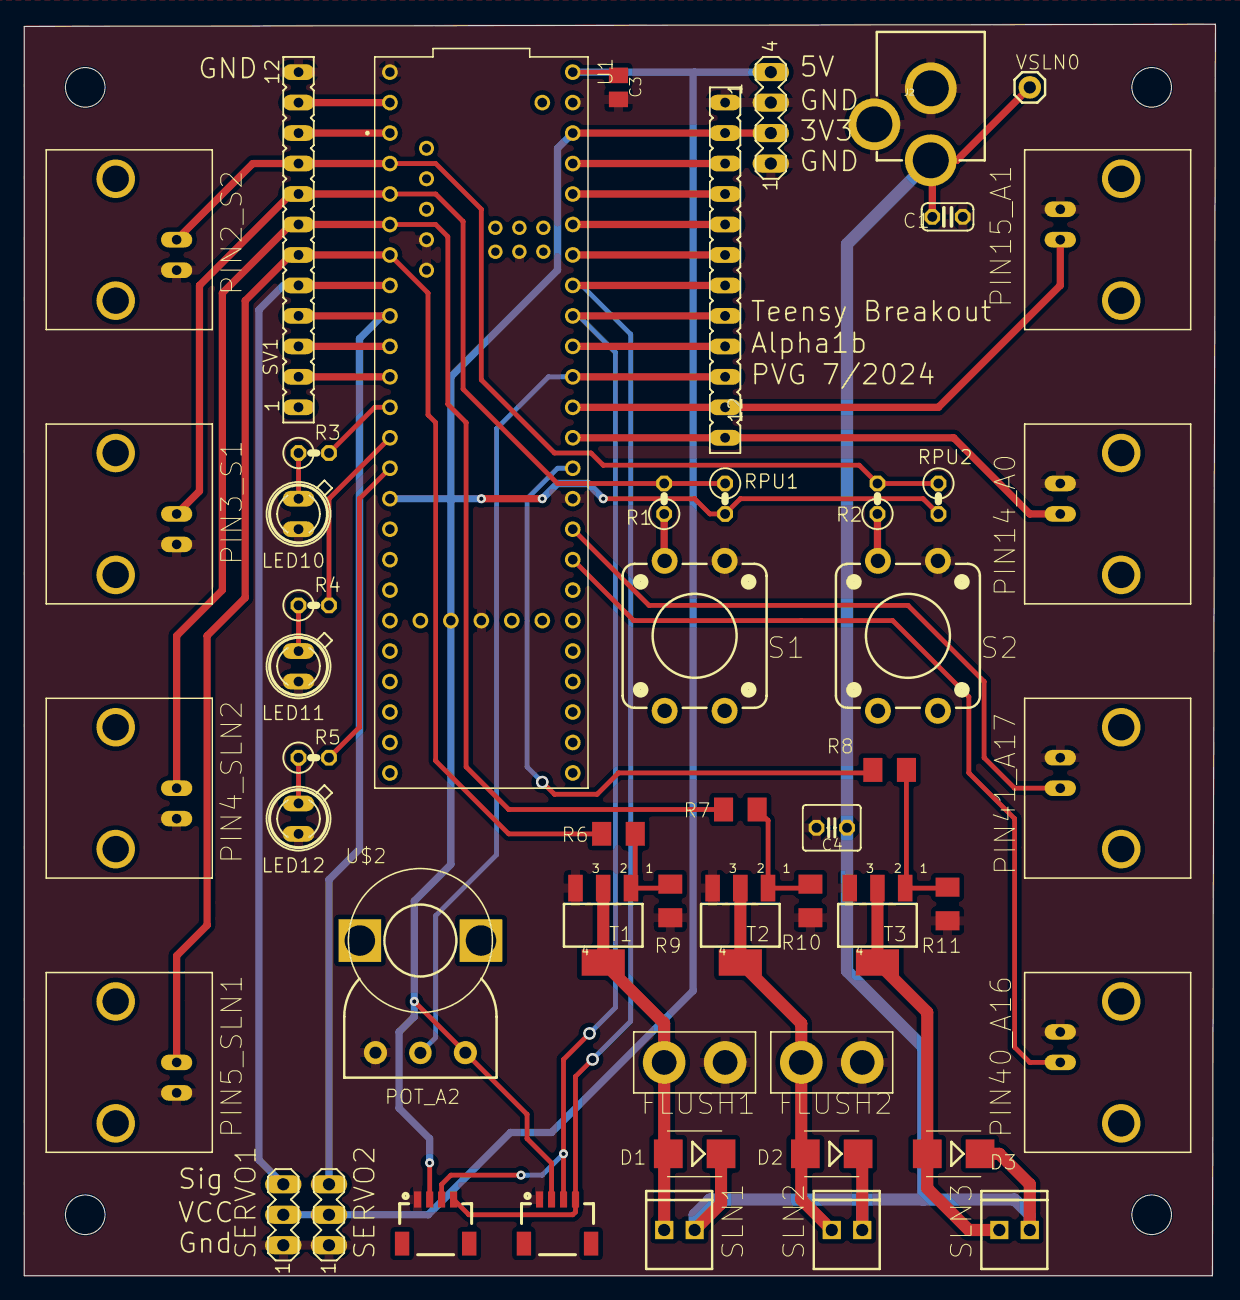
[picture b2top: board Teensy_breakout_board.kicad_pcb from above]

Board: 2 copper layers, 99.3 x 104.3 mm, 55 parts (0 on the bottom side), 41 nets.

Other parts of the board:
@HOLE0, @HOLE1, @HOLE2, @HOLE3: (no value)
